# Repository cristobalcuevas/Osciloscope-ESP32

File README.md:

# Osciloscope with ESP32

This was my project to get my degree :)

It was based on designing a board that could do the acquisition and conditioning of analog signals so that later they would be read by the ESP32 and displayed on a local server within the memory of the ESP32, so that several devices could access through the IP simultaneously.

## Circuit

## PCB Design

### Front Layer

### Back Layer

## Video

<a href="https://drive.google.com/file/d/1jKXpbea2SFpHbxWFMag4WS3YogWa_oBE/view?usp=sharing" target="_blank">Video Google Drive</a>

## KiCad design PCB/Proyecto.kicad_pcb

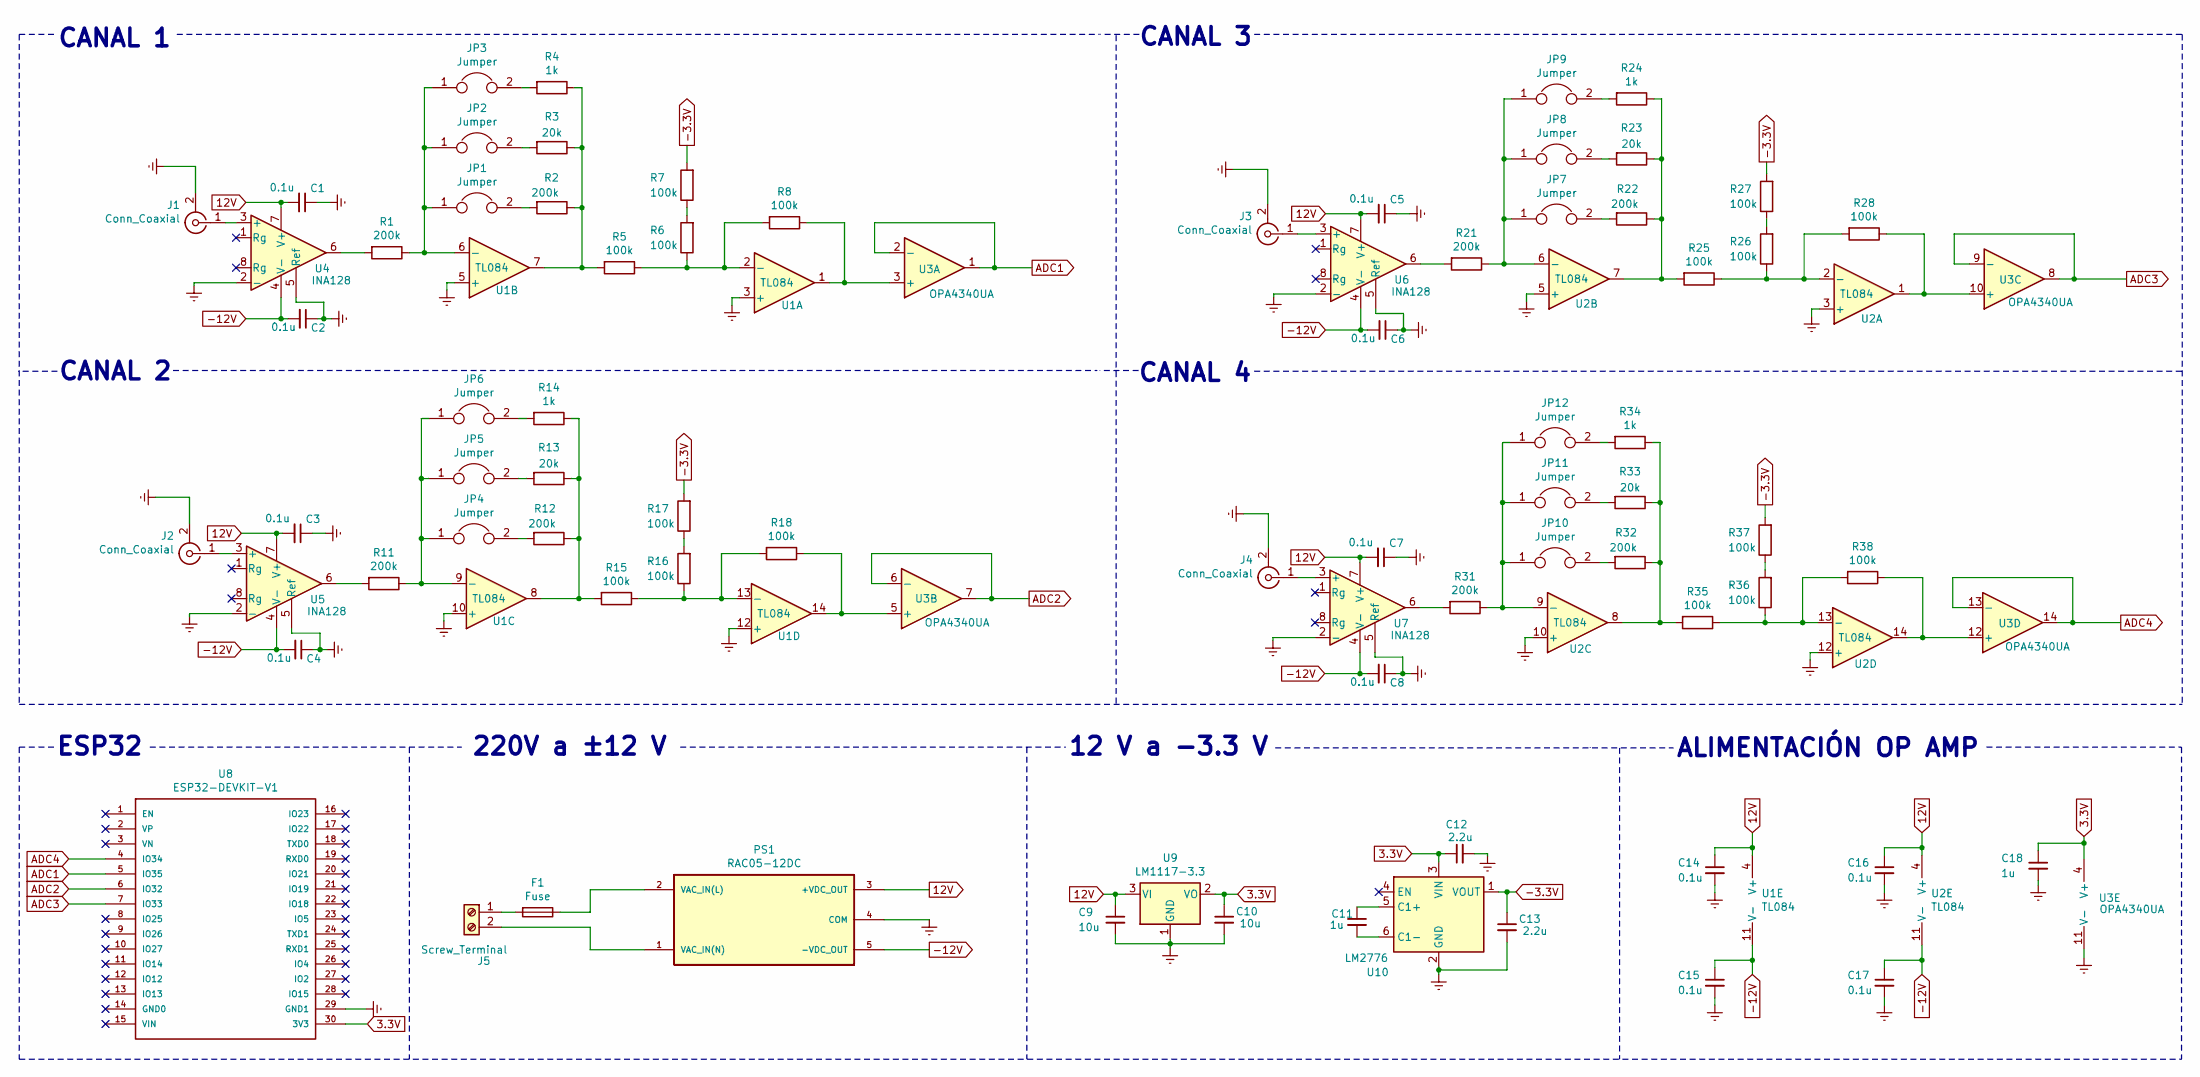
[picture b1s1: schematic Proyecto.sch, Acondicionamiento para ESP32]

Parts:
C1, C2, C3, C4, C5, C6, C7, C8, C14, C15, C16, C17: 0.1u; CP_EIA-3216-18_Kemet-A; Digikey 399-3677-1-ND
C9: 10u; C_1206_3216Metric; Digikey 399-1043-1-ND
C10: 10u; C_1206_3216Metric; Digikey 399-4873-1-ND
C11: 1u; C_1206_3216Metric; Digikey 478-8995-1-ND
C12, C13: 2.2u; C_1206_3216Metric; Digikey 478-13259-1-ND
C18: 1u; CP_EIA-3216-18_Kemet-A; Digikey 399-3677-1-ND
F1: Fuse; Fuseholder_Cylinder-5x20mm_Schurter_0031_8201_Horizontal_Op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; Digikey 507-1286-ND
J1, J2, J3, J4: Conn_Coaxial; BNC_TEConnectivity_1478204_Vertical
J5: Screw_Terminal; Terminal_Block; Digikey 277-6405-ND
JP1, JP2, JP3, JP4, JP5, JP6, JP7, JP8, JP9, JP10, JP11, JP12: Jumper; PinHeader_1x02_P2.54mm_Vertical_SMD_Pin1Left
PS1: RAC05-12DC; RAC05_12DC
R1, R2, R11, R12, R21, R22, R31, R32: 200k; R_0805_2012Metric
R3, R13, R23, R33: 20k; R_0805_2012Metric
R4, R14, R24, R34: 1k; R_0805_2012Metric
R5, R6, R7, R8, R15, R16, R17, R18, R25, R26, R27, R28, R35, R36, R37, R38: 100k; R_0805_2012Metric
U1, U2: TL084; TSSOP-14_4.4x5mm_P0.65mm
U3: OPA4340UA; SOIC-14_3.9x8.7mm_P1.27mm
U4, U5, U6, U7: INA128; SOIC-8_3.9x4.9mm_P1.27mm
U8: ESP32-DEVKIT-V1; ESP_32
U9: LM1117-3.3; SOT-223-3_TabPin2
U10: LM2776; SOT-23-6

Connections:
3.3V: C10.1, C12.1, C18.1, U3.4 (V+), U8.30 (3V3), U9.2 (VO), U10.3 (VIN)
12V: C1.2, C3.2, C5.2, C7.2, C9.1, C14.1, C16.1, PS1.3 (+VDC_OUT), U1.4 (V+), U2.4 (V+), U4.7 (V+), U5.7 (V+), U6.7 (V+), U7.7 (V+), U9.3 (VI)
-3.3V: C13.1, R7.2, R17.2, R27.2, R37.2, U10.1 (VOUT)
-12V: C2.2, C4.2, C6.2, C8.2, C15.1, C17.1, PS1.5 (-VDC_OUT), U1.11 (V-), U2.11 (V-), U4.4 (V-), U5.4 (V-), U6.4 (V-), U7.4 (V-)
ADC1: U3.1, U3.2 (-), U8.5 (IO35)
ADC2: U3.6 (-), U3.7, U8.6 (IO32)
ADC3: U3.8, U3.9 (-), U8.7 (IO33)
ADC4: U3.13 (-), U3.14, U8.4 (IO34)
Earth: C1.1, C2.1, C3.1, C4.1, C5.1, C6.1, C7.1, C8.1, C9.2, C10.2, C12.2, C13.2, C14.2, C15.2, C16.2, C17.2, C18.2, J1.2 (Ext), J2.2 (Ext), J3.2 (Ext), J4.2 (Ext), PS1.4 (COM), U1.3 (+), U1.5 (+), U1.10 (+), U1.12 (+), U2.3 (+), U2.5 (+), U2.10 (+), U2.12 (+), U3.11 (V-), U4.2 (-), U4.5 (Ref), U5.2 (-), U5.5 (Ref), U6.2 (-), U6.5 (Ref), U7.2 (-), U7.5 (Ref), U8.29 (GND1), U9.1 (GND), U10.2 (GND)
unnamed: C11.1, U10.5 (C1+)
unnamed: C11.2, U10.6 (C1-)
unnamed: F1.1, PS1.2 (VAC_IN(L))
unnamed: F1.2, J5.1
unnamed: J1.1 (In), U4.3 (+)
unnamed: J2.1 (In), U5.3 (+)
unnamed: J3.1 (In), U6.3 (+)
unnamed: J4.1 (In), U7.3 (+)
unnamed: J5.2, PS1.1 (VAC_IN(N))
unnamed: JP1.1, JP2.1, JP3.1, R1.1, U1.6 (-)
unnamed: JP1.2, R2.2
unnamed: JP2.2, R3.2
unnamed: JP3.2, R4.2
unnamed: JP4.1, JP5.1, JP6.1, R11.1, U1.9 (-)
unnamed: JP4.2, R12.2
unnamed: JP5.2, R13.2
unnamed: JP6.2, R14.2
unnamed: JP7.1, JP8.1, JP9.1, R21.1, U2.6 (-)
unnamed: JP7.2, R22.2
unnamed: JP8.2, R23.2
unnamed: JP9.2, R24.2
unnamed: JP10.1, JP11.1, JP12.1, R31.1, U2.9 (-)
unnamed: JP10.2, R32.2
unnamed: JP11.2, R33.2
unnamed: JP12.2, R34.2
unnamed: R1.2, U4.6
unnamed: R2.1, R3.1, R4.1, R5.2, U1.7
unnamed: R5.1, R6.1, R8.2, U1.2 (-)
unnamed: R6.2, R7.1
unnamed: R8.1, U1.1, U3.3 (+)
unnamed: R11.2, U5.6
unnamed: R12.1, R13.1, R14.1, R15.2, U1.8
unnamed: R15.1, R16.1, R18.2, U1.13 (-)
unnamed: R16.2, R17.1
unnamed: R18.1, U1.14, U3.5 (+)
unnamed: R21.2, U6.6
unnamed: R22.1, R23.1, R24.1, R25.2, U2.7
unnamed: R25.1, R26.1, R28.2, U2.2 (-)
unnamed: R26.2, R27.1
unnamed: R28.1, U2.1, U3.10 (+)
unnamed: R31.2, U7.6
unnamed: R32.1, R33.1, R34.1, R35.2, U2.8
unnamed: R35.1, R36.1, R38.2, U2.13 (-)
unnamed: R36.2, R37.1
unnamed: R38.1, U2.14, U3.12 (+)

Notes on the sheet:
CANAL 1
CANAL 3
CANAL 4
220V a ±12 V
12 V a -3.3 V
ESP32
CANAL 2
ALIMENTACIÓN OP AMP

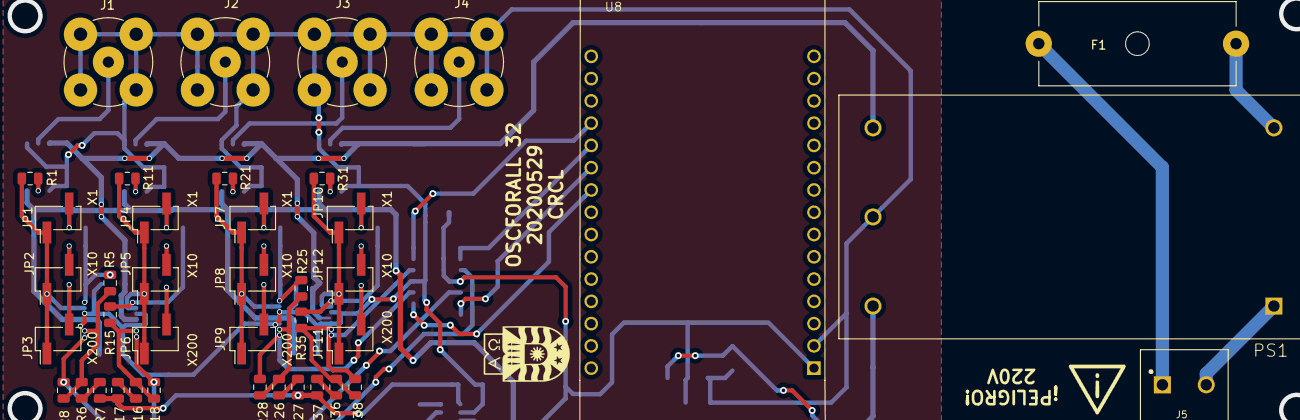
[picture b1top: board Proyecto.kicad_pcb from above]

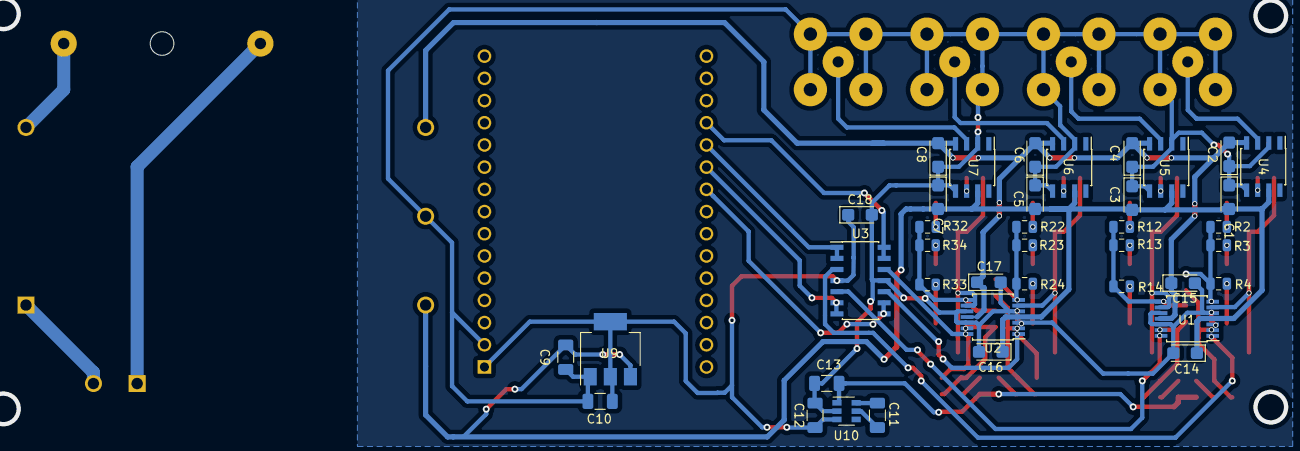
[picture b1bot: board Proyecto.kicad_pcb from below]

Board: 2 copper layers, 79 parts (39 on the bottom side), 54 nets.
